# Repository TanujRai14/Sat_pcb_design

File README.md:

# Can Satellite PCB Design

This repository contains the PCB design files and documentation for a Can Satellite, featuring multiple environmental and orientation sensors, power management, and wireless communication capabilities. The board is designed for compactness and reliability, suitable for satellite and high-altitude balloon missions.

---

## Sensors Integrated

- **BMP280**: Pressure and temperature sensor  
- **MPU6050**: Accelerometer and gyroscope  
- **LM35**: Analog temperature sensor  
- **MQ135**: Air quality/gas sensor  
- **DHT11**: Temperature and humidity sensor  

## Key Components

- **ESP32**  
  - Handles main processing  
  - Supports I2C and SPI communication for peripherals  
- **TP4056 Charging Module**  
  - Li-ion battery charging management  
- **AMS1117**  
  - 3.3V voltage regulator  
- **LoRa SX1278**  
  - Long-range wireless communication module  

---

## PCB Design Details

- **Track Widths**  
  - **5V Supply:** 0.5 mm  
  - **3.3V Supply:** 0.3 mm  
  - **Signal Traces:** 0.2 mm  

- **Layer Stackup**
  - **Top Layer:** Signals and GND  
  - **First Inner Layer:** GND plane  
  - **Second Inner Layer:** Power plane  
  - **Bottom Layer:** Signals and 5V pad  

---

## Power Management

- **Input:** Li-ion battery (managed by TP4056)
- **Regulation:** AMS1117 provides 3.3V for logic and sensors
- **Separate power and ground planes** for noise reduction and stable operation

---

## Communication

- **LoRa SX1278** for long-range, low-power wireless data transmission
- **ESP32** serves as the central controller, interfacing with sensors and modules via I2C/SPI

---

## Notes

- Carefully matched track widths for power and signal integrity
- Dedicated inner layers for ground and power to minimize noise
- Suitable for CubeSat, CanSat, and other small satellite or experimental payloads

## Photos

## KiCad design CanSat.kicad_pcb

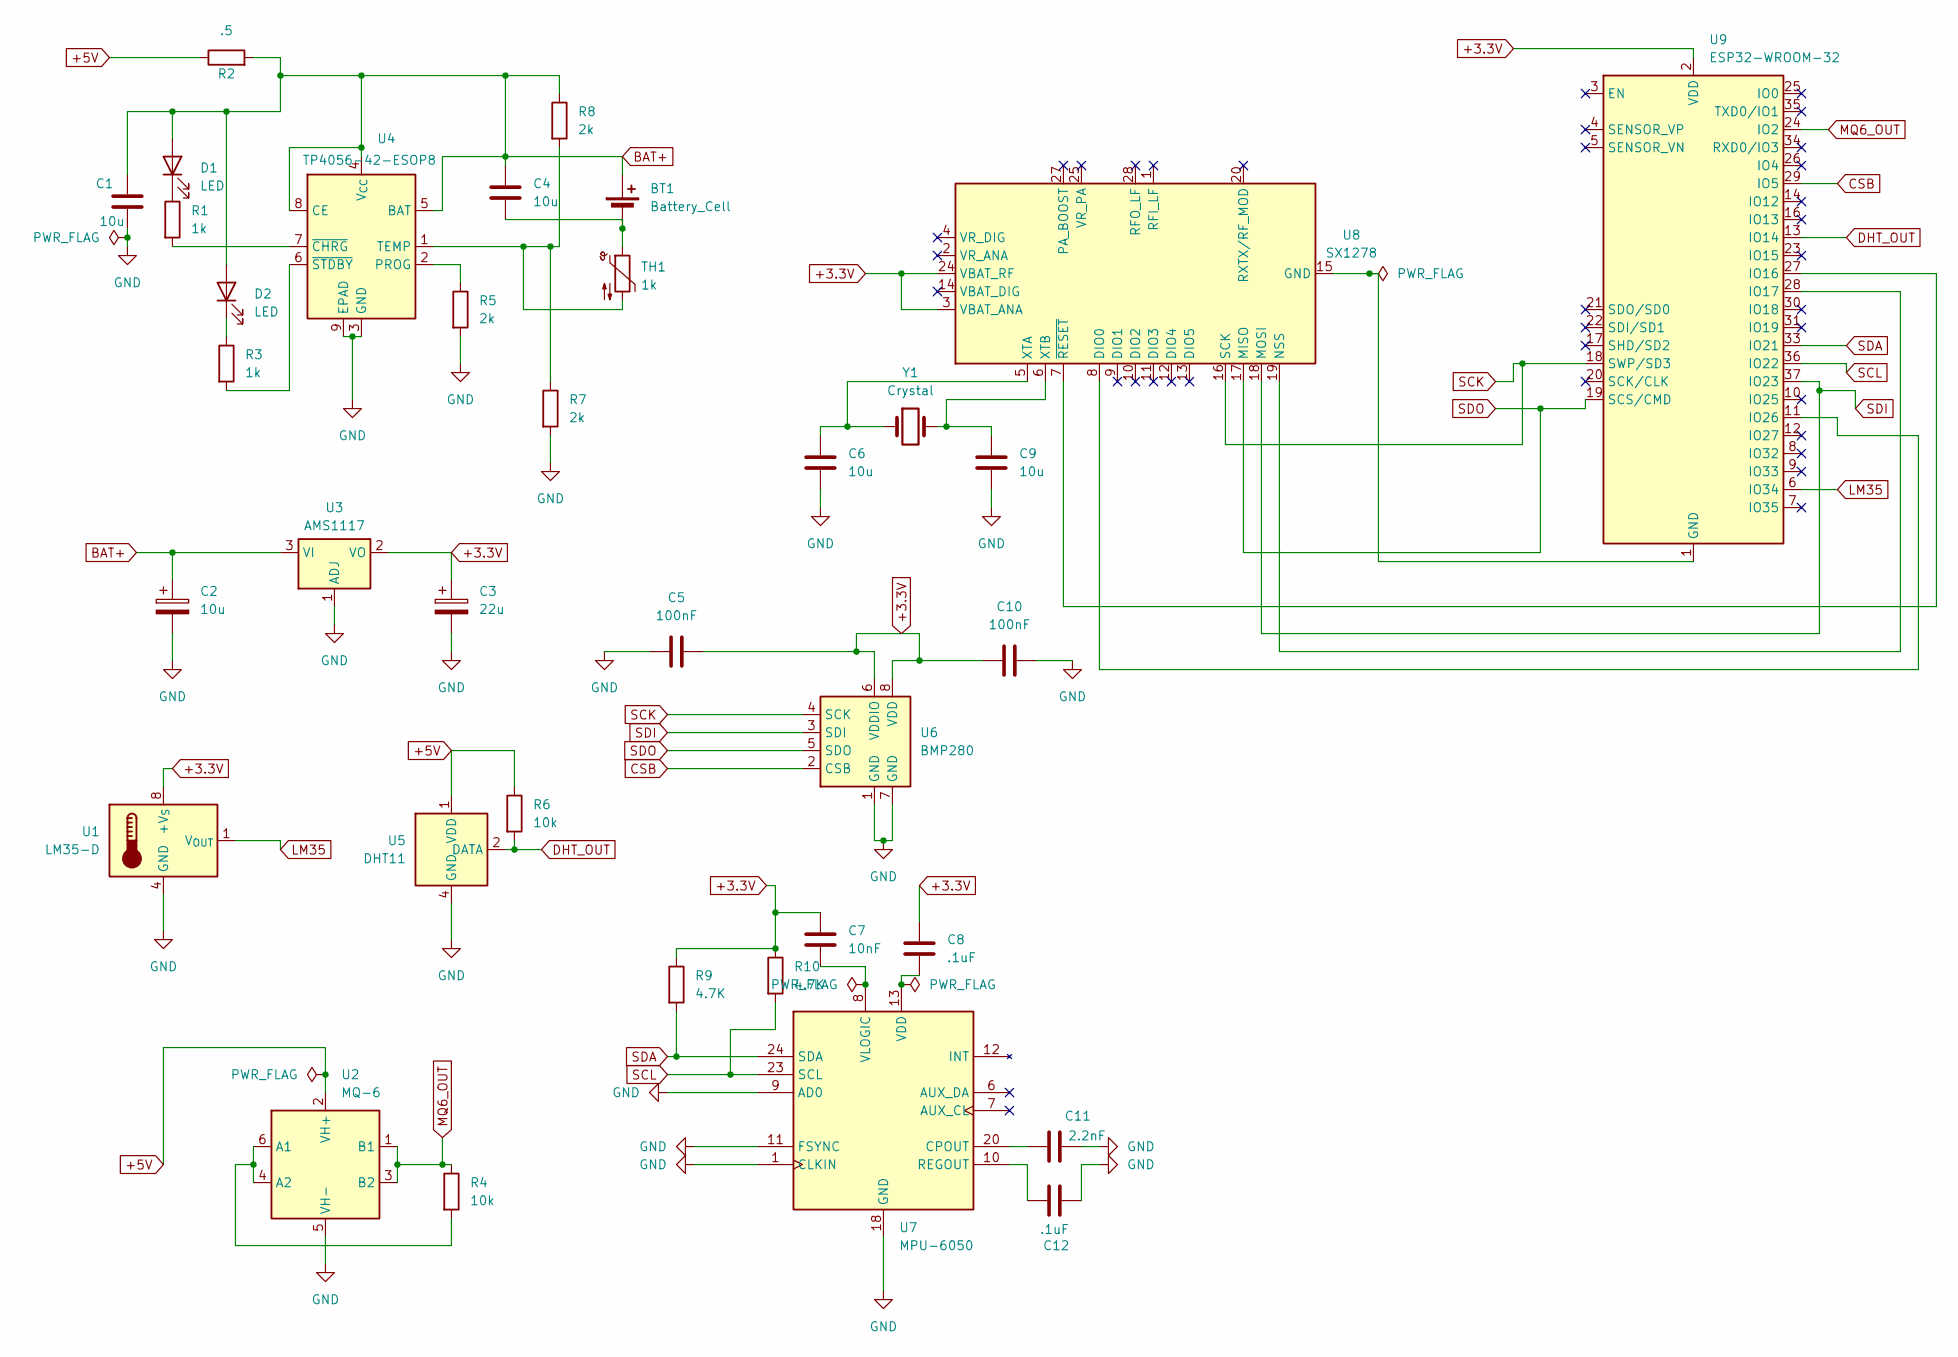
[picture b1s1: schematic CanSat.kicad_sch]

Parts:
BT1: Battery_Cell
C1, C4, C6, C9: 10u; C_0805_2012Metric
C2: 10u; CP_Radial_D10.0mm_P5.00mm
C3: 22u; CP_Radial_D10.0mm_P5.00mm
C5, C10: 100nF; C_0805_2012Metric
C7: 10nF; C_0805_2012Metric
C8, C12: .1uF; C_0805_2012Metric
C11: 2.2nF; C_0805_2012Metric
D1, D2: LED; LED_0805_2012Metric
R1, R3: 1k; R_0805_2012Metric
R2: .5; R_0805_2012Metric
R4, R6: 10k; R_0805_2012Metric
R5, R7, R8: 2k; R_0805_2012Metric
R9, R10: 4.7K; R_0805_2012Metric
TH1: 1k; R_0805_2012Metric
U1: LM35-D; SOIC-8_3.9x4.9mm_P1.27mm
U2: MQ-6
U3: AMS1117; SOT-223-3_TabPin2
U4: TP4056-42-ESOP8; SOIC-8-1EP_3.9x4.9mm_P1.27mm_EP2.41x3.3mm_ThermalVias
U5: DHT11; Aosong_DHT11_5.5x12.0_P2.54mm
U6: BMP280; Bosch_LGA-8_2x2.5mm_P0.65mm_ClockwisePinNumbering
U7: MPU-6050; InvenSense_QFN-24_4x4mm_P0.5mm
U8: SX1278; QFN-28-1EP_6x6mm_P0.65mm_EP4.8x4.8mm
U9: ESP32-WROOM-32
Y1: Crystal; Crystal_SMD_Abracon_ABM7-2Pin_6.0x3.5mm

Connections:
+3.3V: C3.1, C5.2, C7.2, C8.1, C10.1, R9.1, R10.1, U1.8 (+V_{S}), U3.2 (VO), U6.6 (VDDIO), U6.8 (VDD), U8.3 (VBAT_ANA), U8.24 (VBAT_RF), U9.2 (VDD)
+5V: R2.1, R6.1, U2.2 (VH+), U5.1 (VDD)
BAT+: BT1.1 (+), C1.1, C2.1, C4.1, D1.2 (A), D2.2 (A), R2.2, R8.1, U3.3 (VI), U4.4 (V_{CC}), U4.5 (BAT), U4.8 (CE)
CSB: U6.2 (CSB), U9.29 (IO5)
DHT_OUT: R6.2, U5.2 (DATA), U9.13 (IO14)
GND: C1.2, C2.2, C3.2, C5.1, C6.2, C9.2, C10.2, C11.2, C12.2, R5.2, R7.2, U1.4 (GND), U2.5 (VH-), U3.1 (ADJ), U4.3 (GND), U4.9 (EPAD), U5.4 (GND), U6.1 (GND), U6.7 (GND), U7.1 (CLKIN), U7.9 (AD0), U7.11 (FSYNC), U7.18 (GND)
LM35: U1.1 (V_{OUT}), U9.6 (IO34)
MQ6_OUT: R4.1, U2.1 (B1), U2.3 (B2), U9.24 (IO2)
unnamed: BT1.2 (-), C4.2, TH1.1
unnamed: D1.1 (K), R1.1
unnamed: D2.1 (K), R3.1
unnamed: R4.2, U2.4 (A2), U2.6 (A1)
unnamed: R5.1, U4.2 (PROG)
unnamed: R7.1, R8.2, TH1.2, U4.1 (TEMP)
unnamed: R1.2, U4.7 (~CHRG)
unnamed: R3.2, U4.6 (~STDBY)
unnamed: C11.1, U7.20 (CPOUT)
unnamed: C12.1, U7.10 (REGOUT)
unnamed: C8.2, U7.13 (VDD)
unnamed: C7.1, U7.8 (VLOGIC)
unnamed: U8.8 (DIO0), U9.11 (IO26)
unnamed: U8.15 (GND), U8.21 (GND), U8.22 (GND), U8.23 (GND), U8.26 (GND), U8.29 (GND), U9.1 (GND), U9.15 (GND), U9.38 (GND), U9.39 (GND)
unnamed: U8.19 (NSS), U9.28 (IO17)
unnamed: C6.1, U8.5 (XTA), Y1.1
unnamed: C9.1, U8.6 (XTB), Y1.2
unnamed: U8.7 (~RESET), U9.27 (IO16)
SCK: U6.4 (SCK), U8.16 (SCK), U9.18 (SWP/SD3)
SCL: R10.2, U7.23 (SCL), U9.36 (IO22)
SDA: R9.2, U7.24 (SDA), U9.33 (IO21)
SDI: U6.3 (SDI), U8.18 (MOSI), U9.37 (IO23)
SDO: U6.5 (SDO), U8.17 (MISO), U9.19 (SCS/CMD)

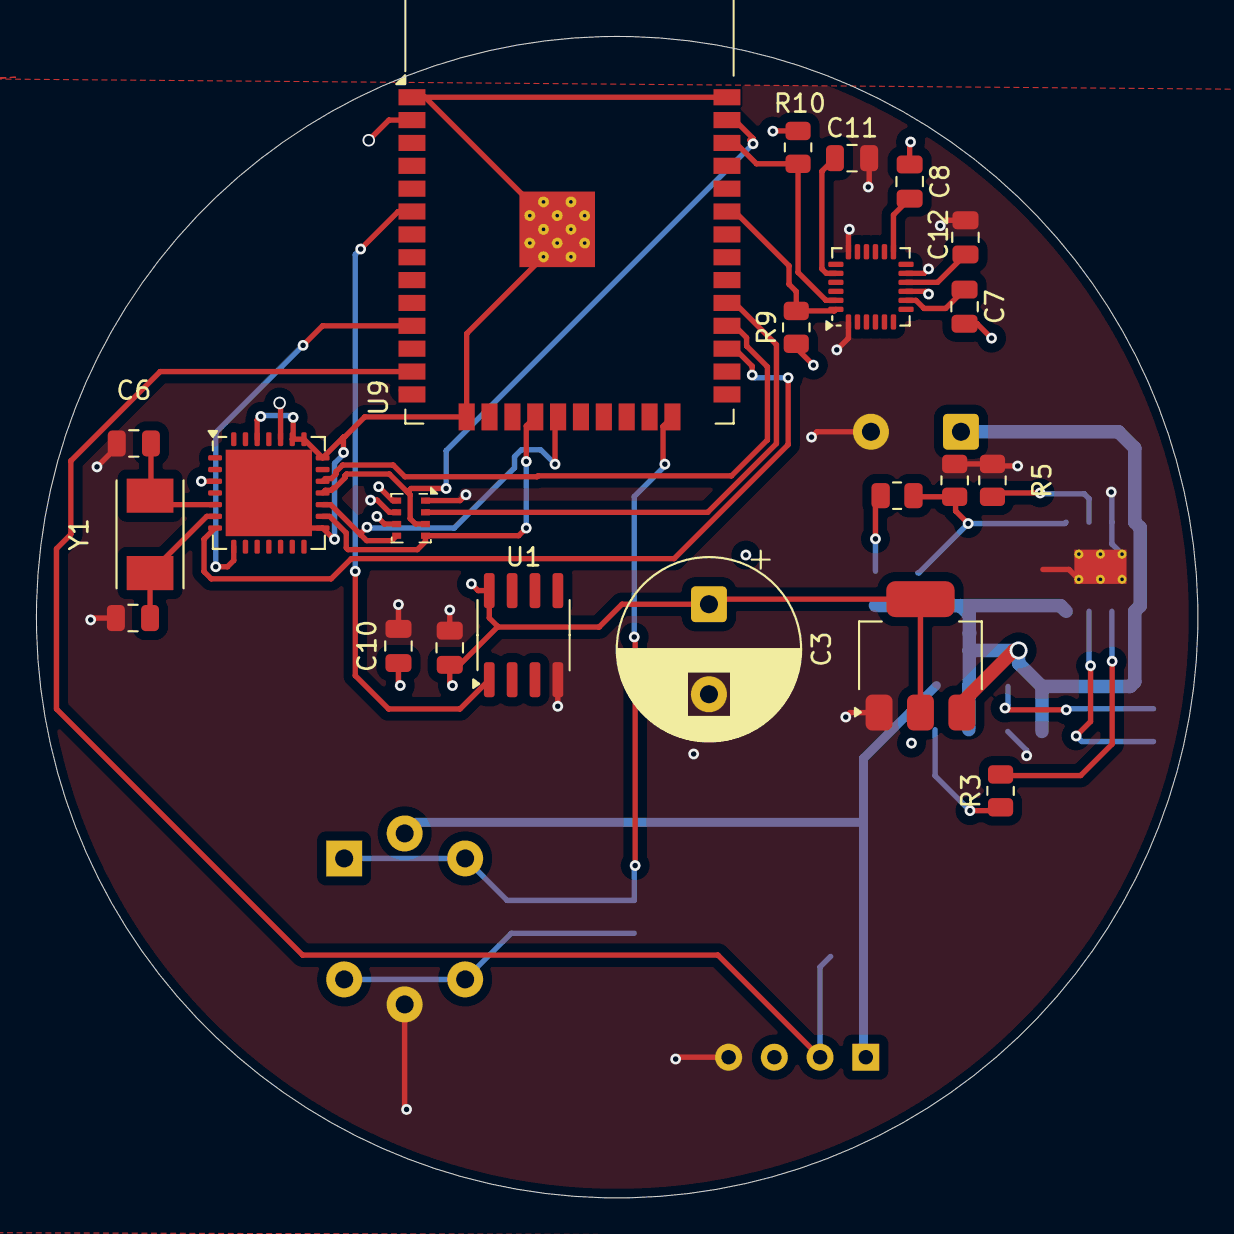
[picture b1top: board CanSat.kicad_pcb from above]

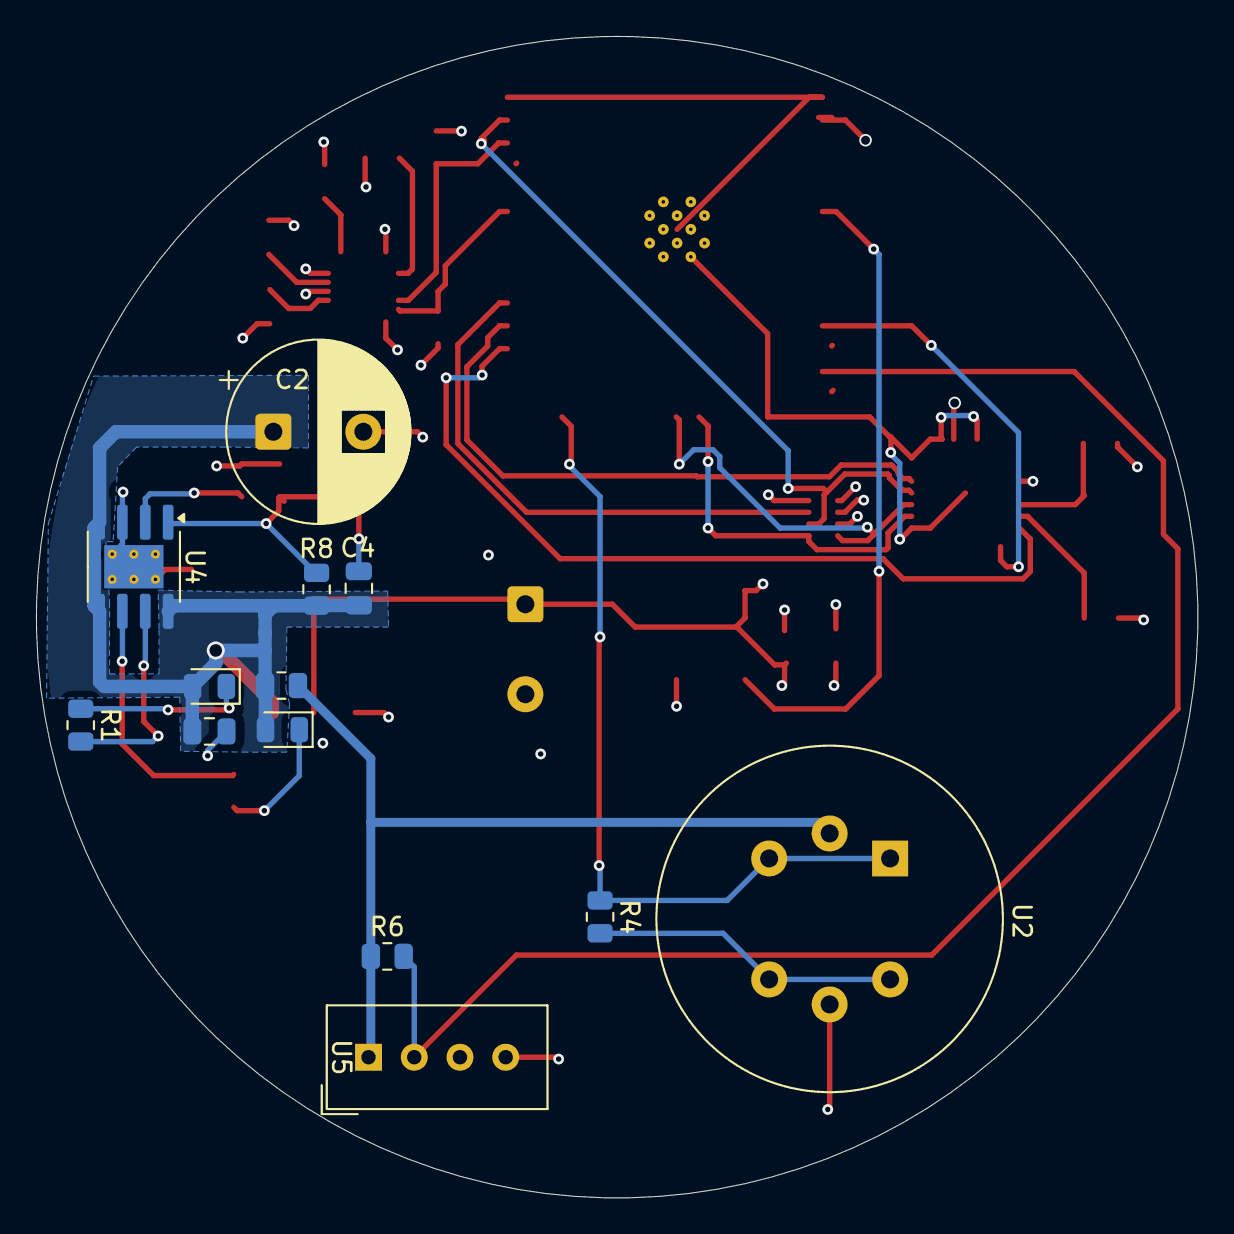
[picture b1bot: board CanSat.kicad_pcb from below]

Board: 4 copper layers, 64.5 x 64.5 mm, 35 parts (13 on the bottom side), 31 nets.

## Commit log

2025-07-17 Create LICENSE
